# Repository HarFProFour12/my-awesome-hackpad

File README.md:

# My Awesome HackPad: 8-Key Macropad

This is my custom mechanical macropad I built from scratch in collaboration with Stardance and Hackclub. It features 8 programmable keys, a rotary encoder for volume adjustments, and an .91" oled display.

## Features

* **8 mechanical switches** for custom macro shortcuts
* **Rotary encoder** with push-button (volume control)
* **oled display** (128x32 I2C)
* **QMK-powered firmware**
* **USB-C connection**
* **Custom 3D-printed body**

## Interface

The macropad connects to the computer using a usb-c cable and acts as a standard keyboard, working with all operating sytems. The macros can be remapped without touching the hardware through the QMK firmware.

The oled display can show live status info and can be also be programmed to show other stuff as well, such as system stats, or custom text.

## 🧠 How It Works

The board is driven by a Seeeduino XIAO RP2040, soldered directly onto the PCB (made from scratch in Kicad). All of the 8 switches is wired in matrix, which is read by the microcontroller. The QMK firmware handles almost everything, with the only things that need configuring being the macros, the hackpad's hardware and metadata and the config.h file.

The rotary encoder and oled display are connected using GPIO pins on the XIAO:
* **Encoder:** Rotation: GP0, GP1, Push Switch: GP2
* **Oled (I2C):** SDA: GP4, SCL: GP6

## Hardware

* **Microcontroller:** Seeed XIAO RP2040
* **Switches:** 8× Mechanical key switches
* **Control:** 1× Rotary encoder with push-button
* **Display:** 0.91" 128x32 oled Display
* **PCB:** Custom 2-layer board designed in KiCad
* **Enclosure:** Custom 3D-printed body and top lid

## Project Structure

```text
my_awesome_hackpad/
├── CAD/
│   ├── hackpad_assembly.step
│   ├── case_top.step
│   └── case_bottom.step
├── PCB/
│   ├── hackpad.kicad_pro
│   ├── hackpad.kicad_sch
│   └── hackpad.kicad_pcb
├── Firmware/
│   └── my_awesome_hackpad/
│       ├── info.json
│       ├── config.h
│       ├── rules.mk
│       └── keymaps/
│           └── default/
│               └── keymap.c
├── production/
│   └── gerbers.zip
└── images/
    ├── hackpad_overall.png
    ├── schematic.png
    ├── pcb_layout.png
    └── case_assembly.pn
```

## Current Status

The project is still under development.

I've done:

* Designing PCB schematic
* PCB layout and routing
* Designing the case in Fusion 360
* Switch and encoder placement
* Case details
* QMK firmware setup

I have left:

* Parts sourcing
* Assembly
* Testing

## Design

The enclosure was 3d modeld in Autodesk Fusion around the layout of the pcb, with cutouts for the keys, the oled and the encoder, and one for the usb-c cable, as well. The enclosure also has some custom engraved text on the outside of the case.

The board layout keeps all 8 switches closely together, along with the oled and encoder positioned on the top for easier access.

## Built With

* KiCad
* Autodesk Fusion 360
* QMK Firmware
* 3D printing
* Collaboration with HackClub - Stardance

## 🤖 AI Usage

I used Claude during the making of this project:

- **KiCad help:** since this was my first time using the software, for help navigating the interface.
- **Code debugging:** fixing issues in the firmware.

The actual PCB design, case design, firmware logic, and assembly were done by me.

---
### Created for Hack Club’s Stardance.
This project was created as part of Hack Club Stardance, a Hack Club event encouraging young people to build and ship their own projects.

---
**Made by Harry Fanouriakis**

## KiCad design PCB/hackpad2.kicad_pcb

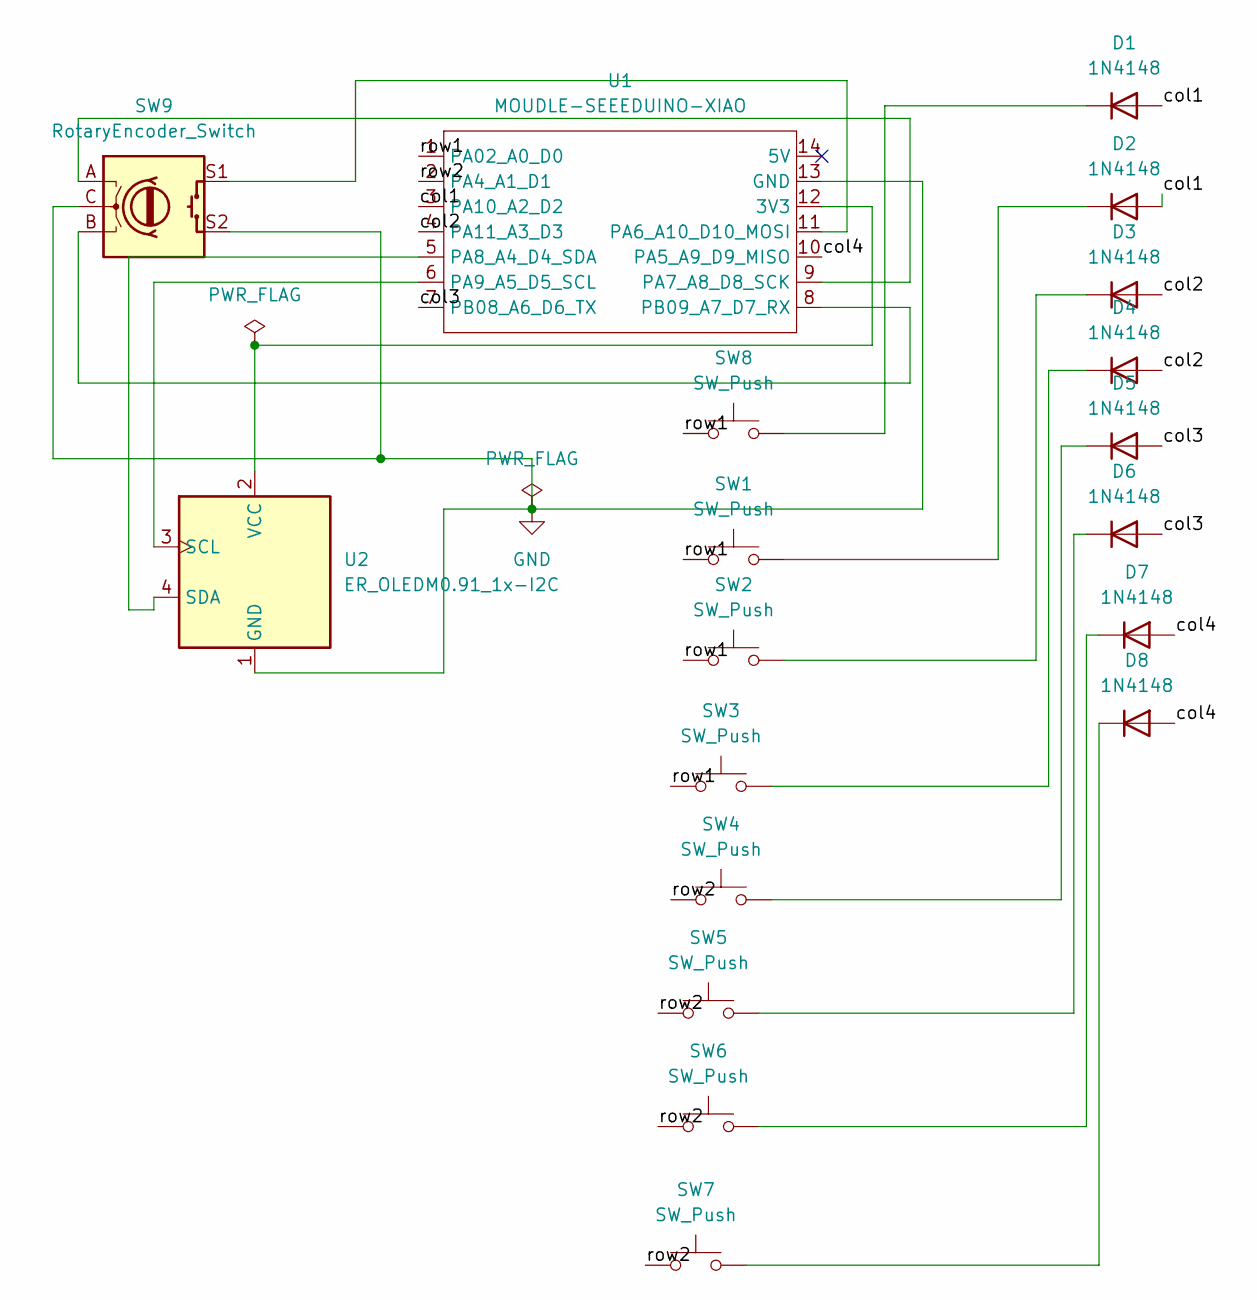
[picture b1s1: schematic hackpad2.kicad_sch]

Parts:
D1, D2, D3, D4, D5, D6, D7, D8: 1N4148; D_DO-35_SOD27_P7.62mm_Horizontal
SW1, SW2, SW3, SW4, SW5, SW6, SW7, SW8: SW_Push; SW_Cherry_MX_1.00u_PCB
SW9: RotaryEncoder_Switch; RotaryEncoder_Alps_EC11E-Switch_Vertical_H20mm
U1: MOUDLE-SEEEDUINO-XIAO; XIAO-Generic-Hybrid-14P-2.54-21X17.8MM
U2: ER_OLEDM0.91_1x-I2C

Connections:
/col1: D1.2 (A), D2.2 (A), U1.3 (PA10_A2_D2)
/col2: D3.2 (A), D4.2 (A), U1.4 (PA11_A3_D3)
/col3: D5.2 (A), D6.2 (A), U1.7 (PB08_A6_D6_TX)
/col4: D7.2 (A), D8.2 (A), U1.10 (PA5_A9_D9_MISO)
/row1: SW1.1, SW2.1, SW3.1, SW8.1, U1.1 (PA02_A0_D0)
/row2: SW4.1, SW5.1, SW6.1, SW7.1, U1.2 (PA4_A1_D1)
GND: SW9.C, SW9.S2, U1.13 (GND), U2.1 (GND)
unnamed: D1.1 (K), SW8.2
unnamed: D2.1 (K), SW1.2
unnamed: D3.1 (K), SW2.2
unnamed: D4.1 (K), SW3.2
unnamed: D5.1 (K), SW4.2
unnamed: D6.1 (K), SW5.2
unnamed: D7.1 (K), SW6.2
unnamed: D8.1 (K), SW7.2
unnamed: U1.12 (3V3), U2.2 (VCC)
unnamed: SW9.S1, U1.11 (PA6_A10_D10_MOSI)
unnamed: SW9.A, U1.9 (PA7_A8_D8_SCK)
unnamed: U1.5 (PA8_A4_D4_SDA), U2.4 (SDA)
unnamed: U1.6 (PA9_A5_D5_SCL), U2.3 (SCL)
unnamed: SW9.B, U1.8 (PB09_A7_D7_RX)

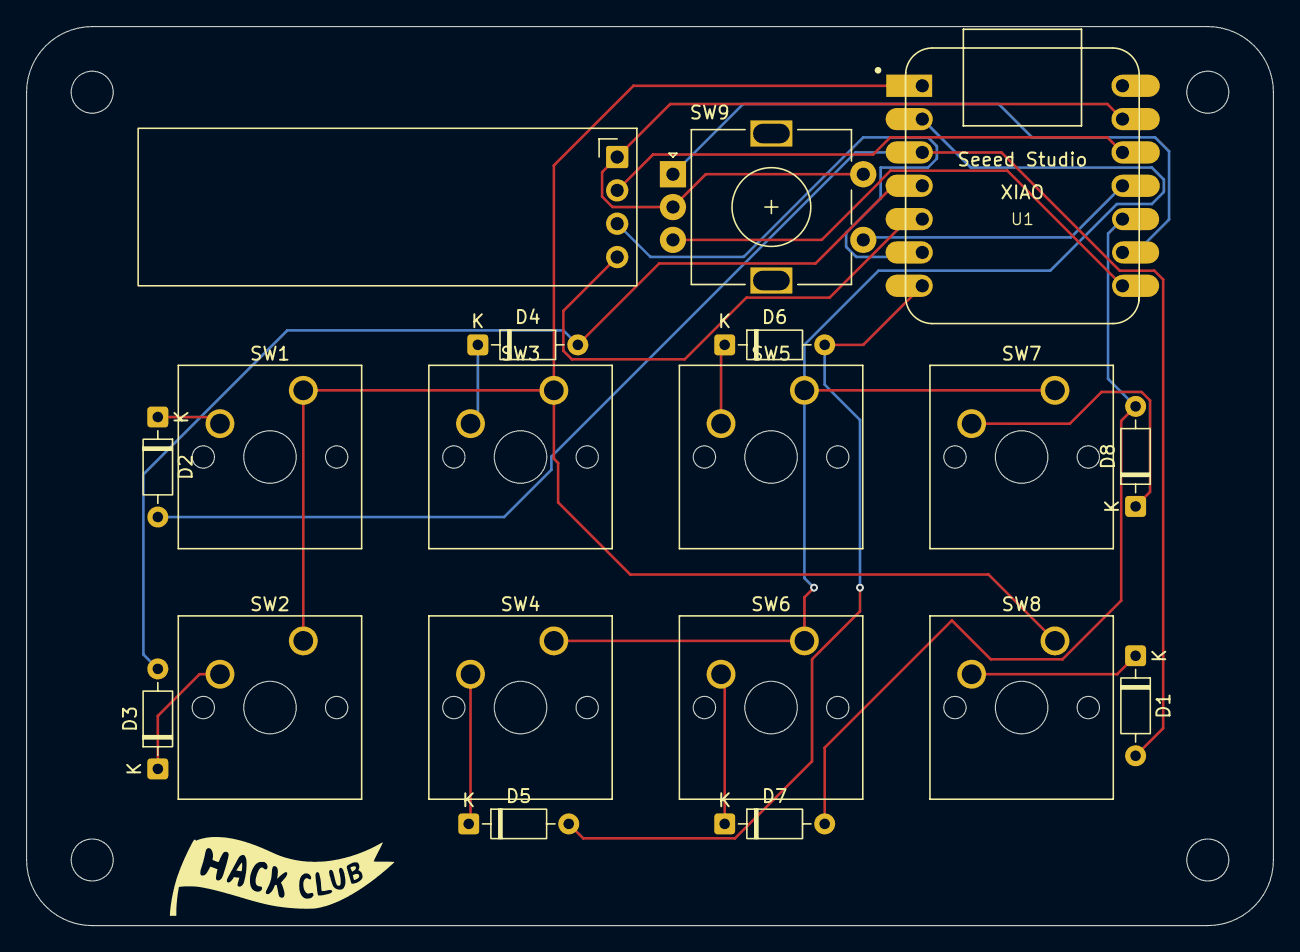
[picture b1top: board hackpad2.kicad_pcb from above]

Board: 2 copper layers, 95.0 x 68.5 mm, 19 parts (0 on the bottom side), 21 nets.
